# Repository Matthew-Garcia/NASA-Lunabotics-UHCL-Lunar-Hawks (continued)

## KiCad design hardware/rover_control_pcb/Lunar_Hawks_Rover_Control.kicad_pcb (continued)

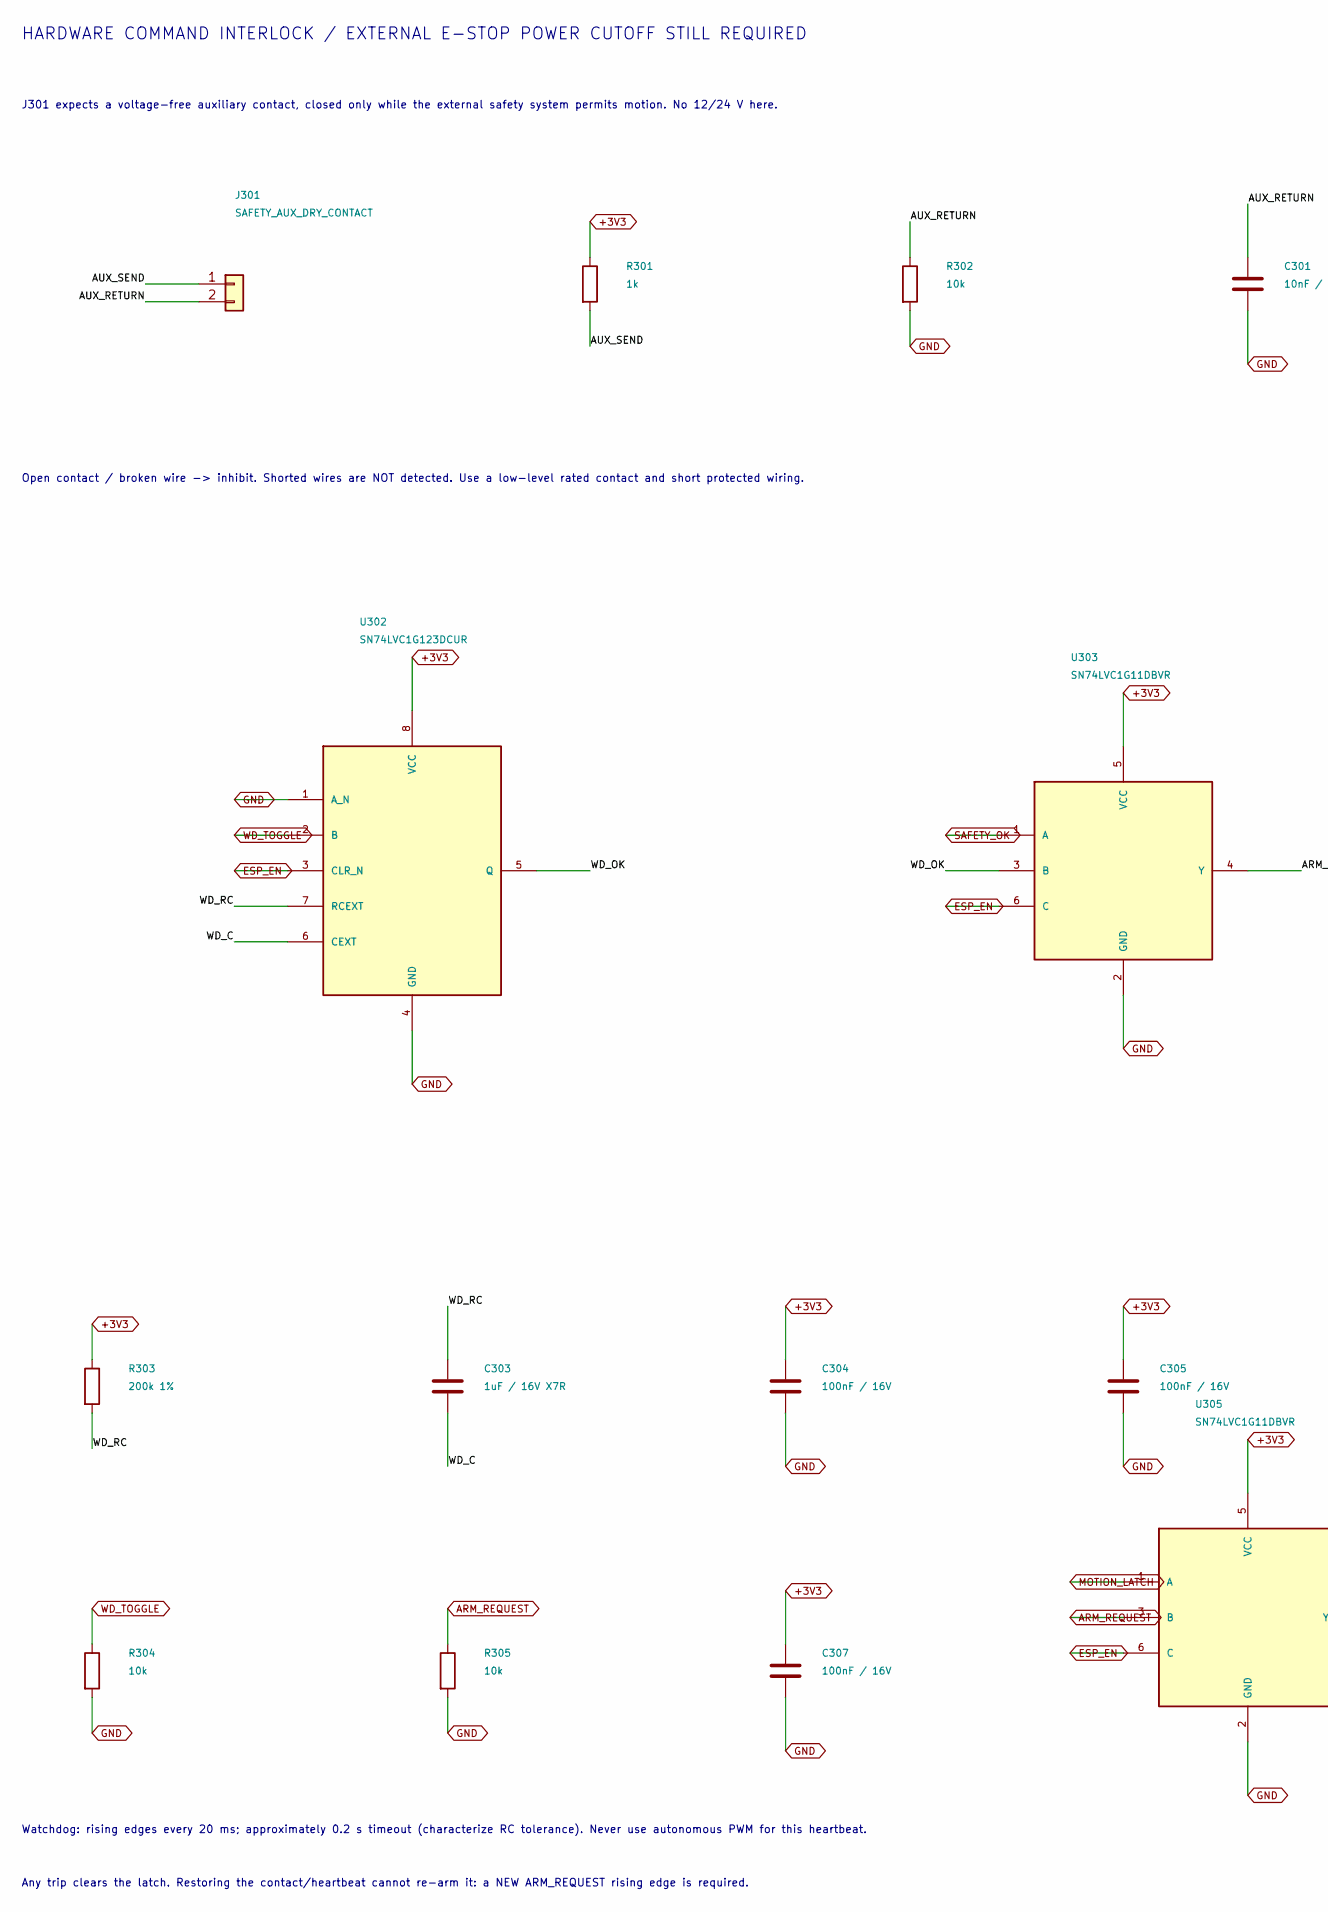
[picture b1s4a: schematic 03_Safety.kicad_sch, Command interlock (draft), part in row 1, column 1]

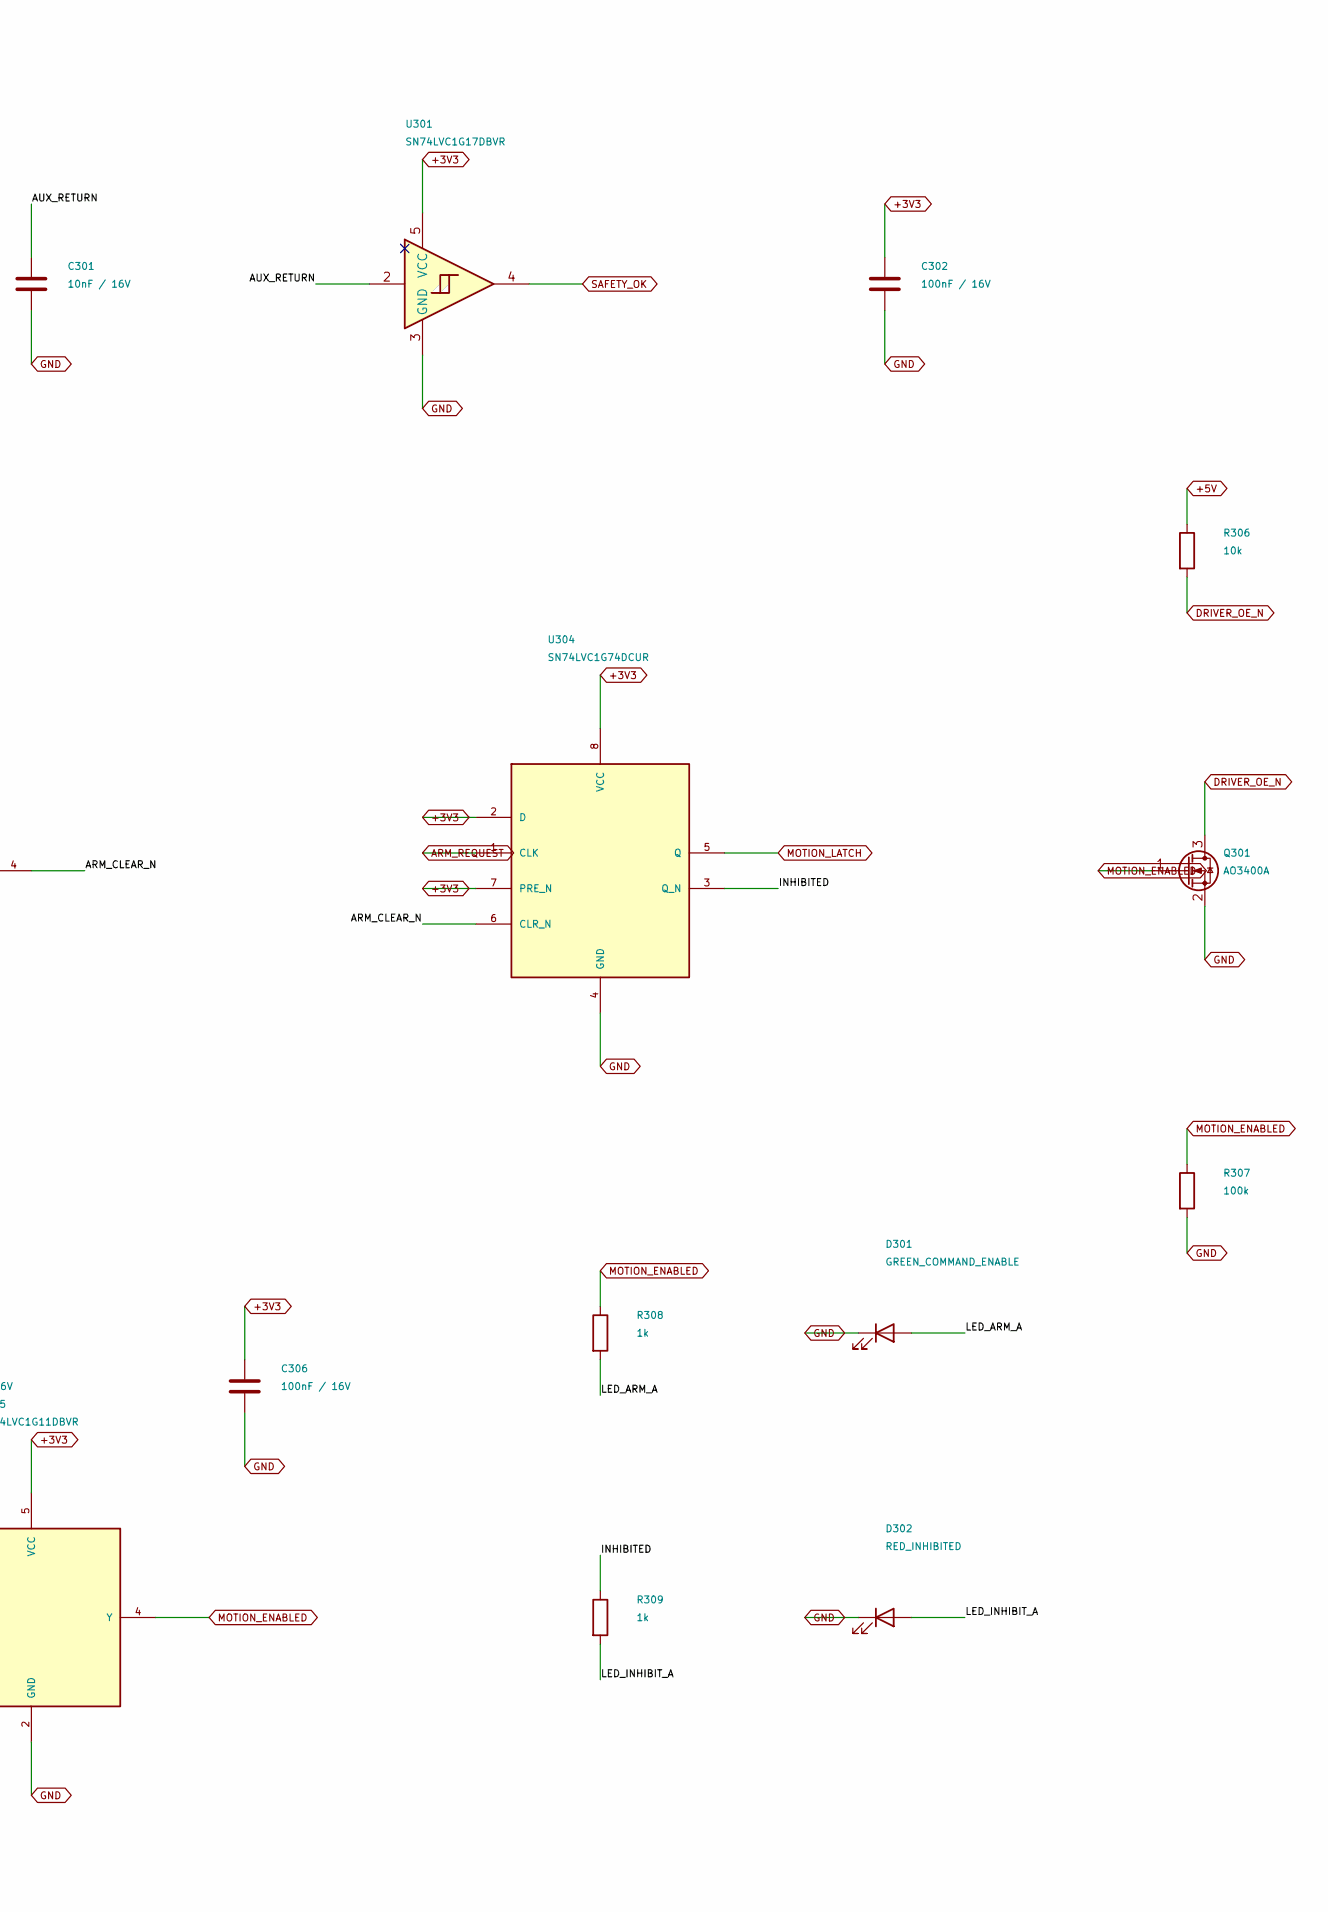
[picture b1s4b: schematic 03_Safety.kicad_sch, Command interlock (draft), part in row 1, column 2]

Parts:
C301: 10nF / 16V; C_0603_1608Metric
C302, C304, C305, C306, C307: 100nF / 16V; C_0603_1608Metric
C303: 1uF / 16V X7R; C_0603_1608Metric
D301: GREEN_COMMAND_ENABLE; LED_0603_1608Metric
D302: RED_INHIBITED; LED_0603_1608Metric
J301: SAFETY_AUX_DRY_CONTACT; TerminalBlock_Phoenix_MKDS-1,5-2_1x02_P5.00mm_Horizontal
Q301: AO3400A; SOT-23
R301, R308, R309: 1k; R_0603_1608Metric
R302, R304, R305, R306: 10k; R_0603_1608Metric
R303: 200k 1%; R_0603_1608Metric
R307: 100k; R_0603_1608Metric
U301: SN74LVC1G17DBVR; SOT-23-5
U302: SN74LVC1G123DCUR; VSSOP-8_2.3x2mm_P0.5mm
U303, U305: SN74LVC1G11DBVR; SOT-23-6
U304: SN74LVC1G74DCUR; VSSOP-8_2.3x2mm_P0.5mm

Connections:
+3V3: C302.1, C304.1, C305.1, C306.1, C307.1, R301.1, R303.1, U301.5 (VCC), U302.8 (VCC), U303.5 (VCC), U304.2 (D), U304.7 (PRE_N), U304.8 (VCC), U305.5 (VCC); also elsewhere on the board
+5V: R306.1; also elsewhere on the board
/Hardware E-stop/ARM_CLEAR_N: U303.4 (Y), U304.6 (CLR_N)
/Hardware E-stop/AUX_RETURN: C301.1, J301.2, R302.1, U301.2
/Hardware E-stop/AUX_SEND: J301.1, R301.2
/Hardware E-stop/INHIBITED: R309.1, U304.3 (Q_N)
/Hardware E-stop/LED_ARM_A: D301.2 (A), R308.2
/Hardware E-stop/LED_INHIBIT_A: D302.2 (A), R309.2
/Hardware E-stop/WD_C: C303.2, U302.6 (CEXT)
/Hardware E-stop/WD_OK: U302.5 (Q), U303.3 (B)
/Hardware E-stop/WD_RC: C303.1, R303.2, U302.7 (RCEXT)
ARM_REQUEST: R305.1, U304.1 (CLK), U305.3 (B); also elsewhere on the board
DRIVER_OE_N: Q301.3 (D), R306.2; also elsewhere on the board
ESP_EN: U302.3 (CLR_N), U303.6 (C), U305.6 (C); also elsewhere on the board
GND: C301.2, C302.2, C304.2, C305.2, C306.2, C307.2, D301.1 (K), D302.1 (K), Q301.2 (S), R302.2, R304.2, R305.2, R307.2, U301.3 (GND), U302.1 (A_N), U302.4 (GND), U303.2 (GND), U304.4 (GND), U305.2 (GND); also elsewhere on the board
MOTION_ENABLED: Q301.1 (G), R307.1, R308.1, U305.4 (Y); also elsewhere on the board
MOTION_LATCH: U304.5 (Q), U305.1 (A)
SAFETY_OK: U301.4, U303.1 (A); also elsewhere on the board
WD_TOGGLE: R304.1, U302.2 (B); also elsewhere on the board

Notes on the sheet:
HARDWARE COMMAND INTERLOCK / EXTERNAL E-STOP POWER CUTOFF STILL REQUIRED
J301 expects a voltage-free auxiliary contact, closed only while the external safety system permits motion. No 12/24 V here.
Open contact / broken wire -> inhibit. Shorted wires are NOT detected. Use a low-level rated contact and short protected wiring.
Watchdog: rising edges every 20 ms; approximately 0.2 s timeout (characterize RC tolerance). Never use autonomous PWM for this heartbeat.
Any trip clears the latch. Restoring the contact/heartbeat cannot re-arm it: a NEW ARM_REQUEST rising edge is required.

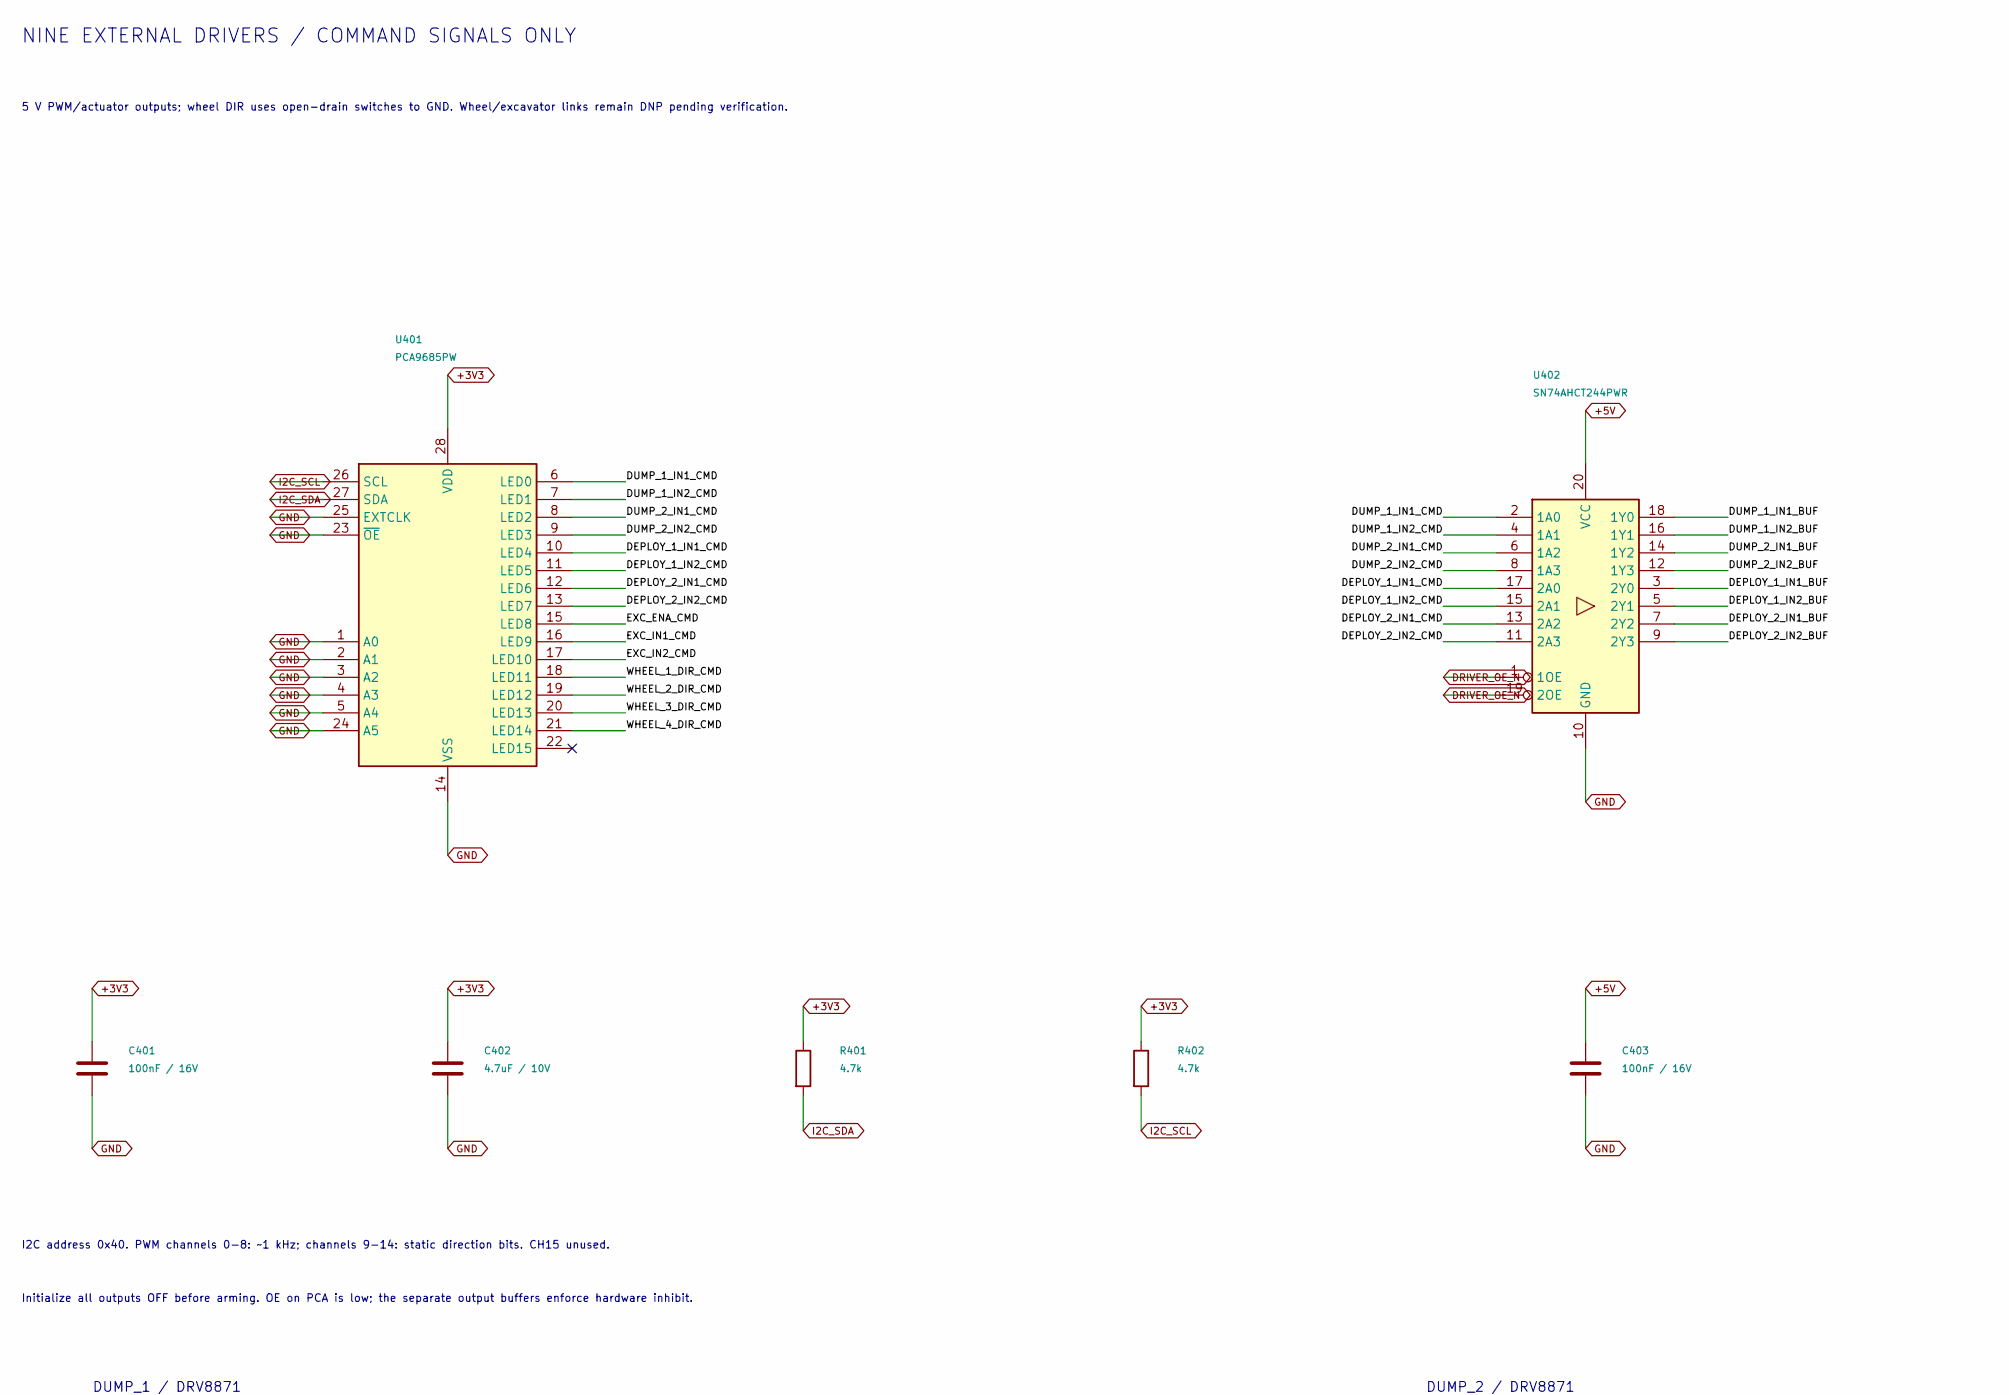
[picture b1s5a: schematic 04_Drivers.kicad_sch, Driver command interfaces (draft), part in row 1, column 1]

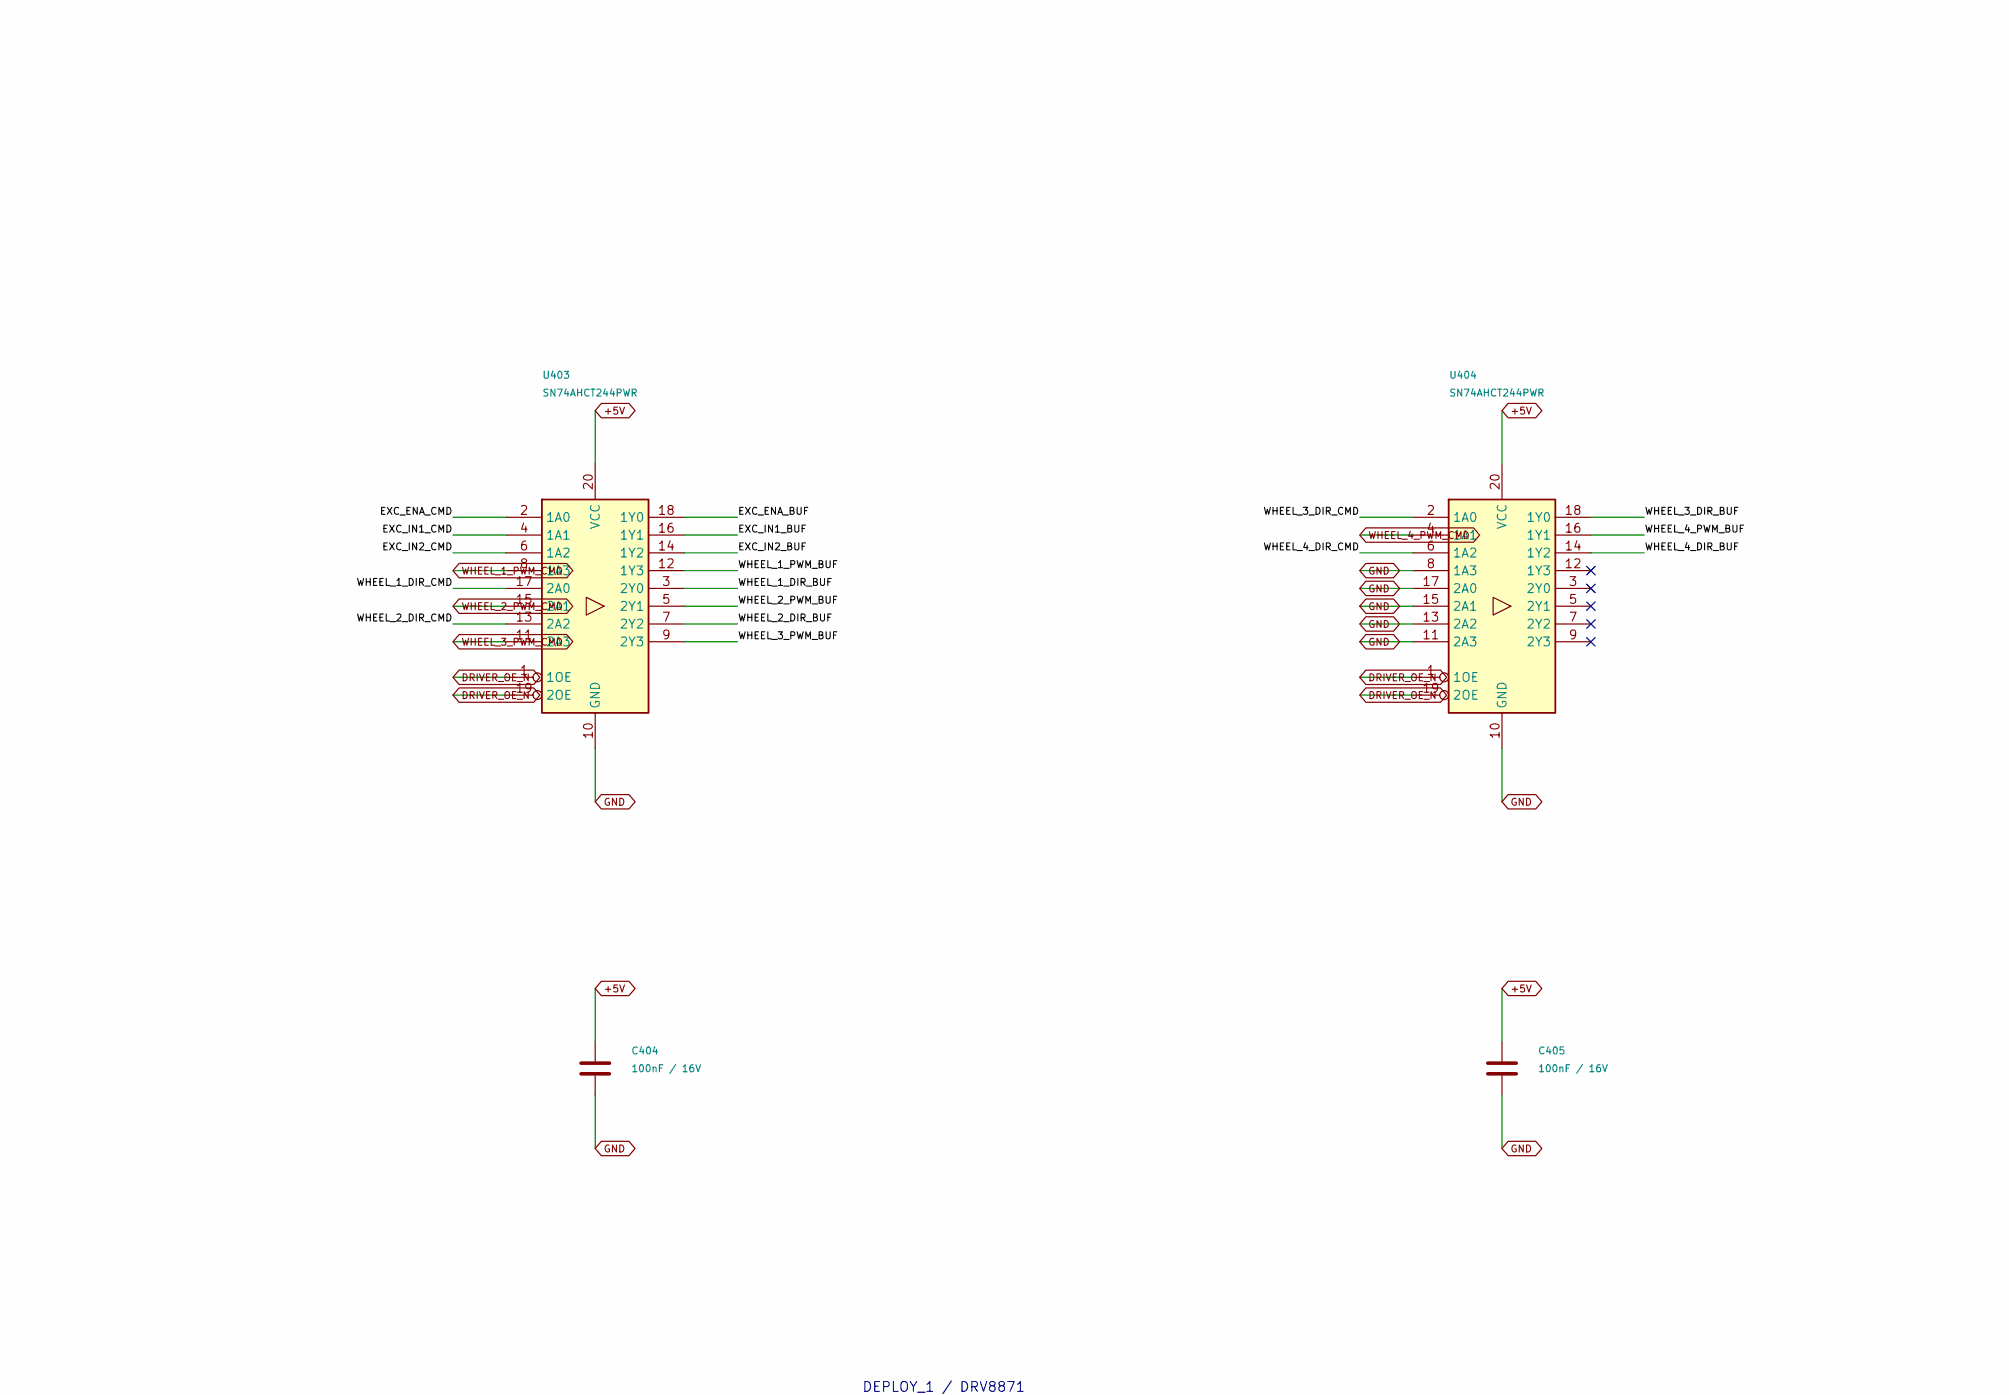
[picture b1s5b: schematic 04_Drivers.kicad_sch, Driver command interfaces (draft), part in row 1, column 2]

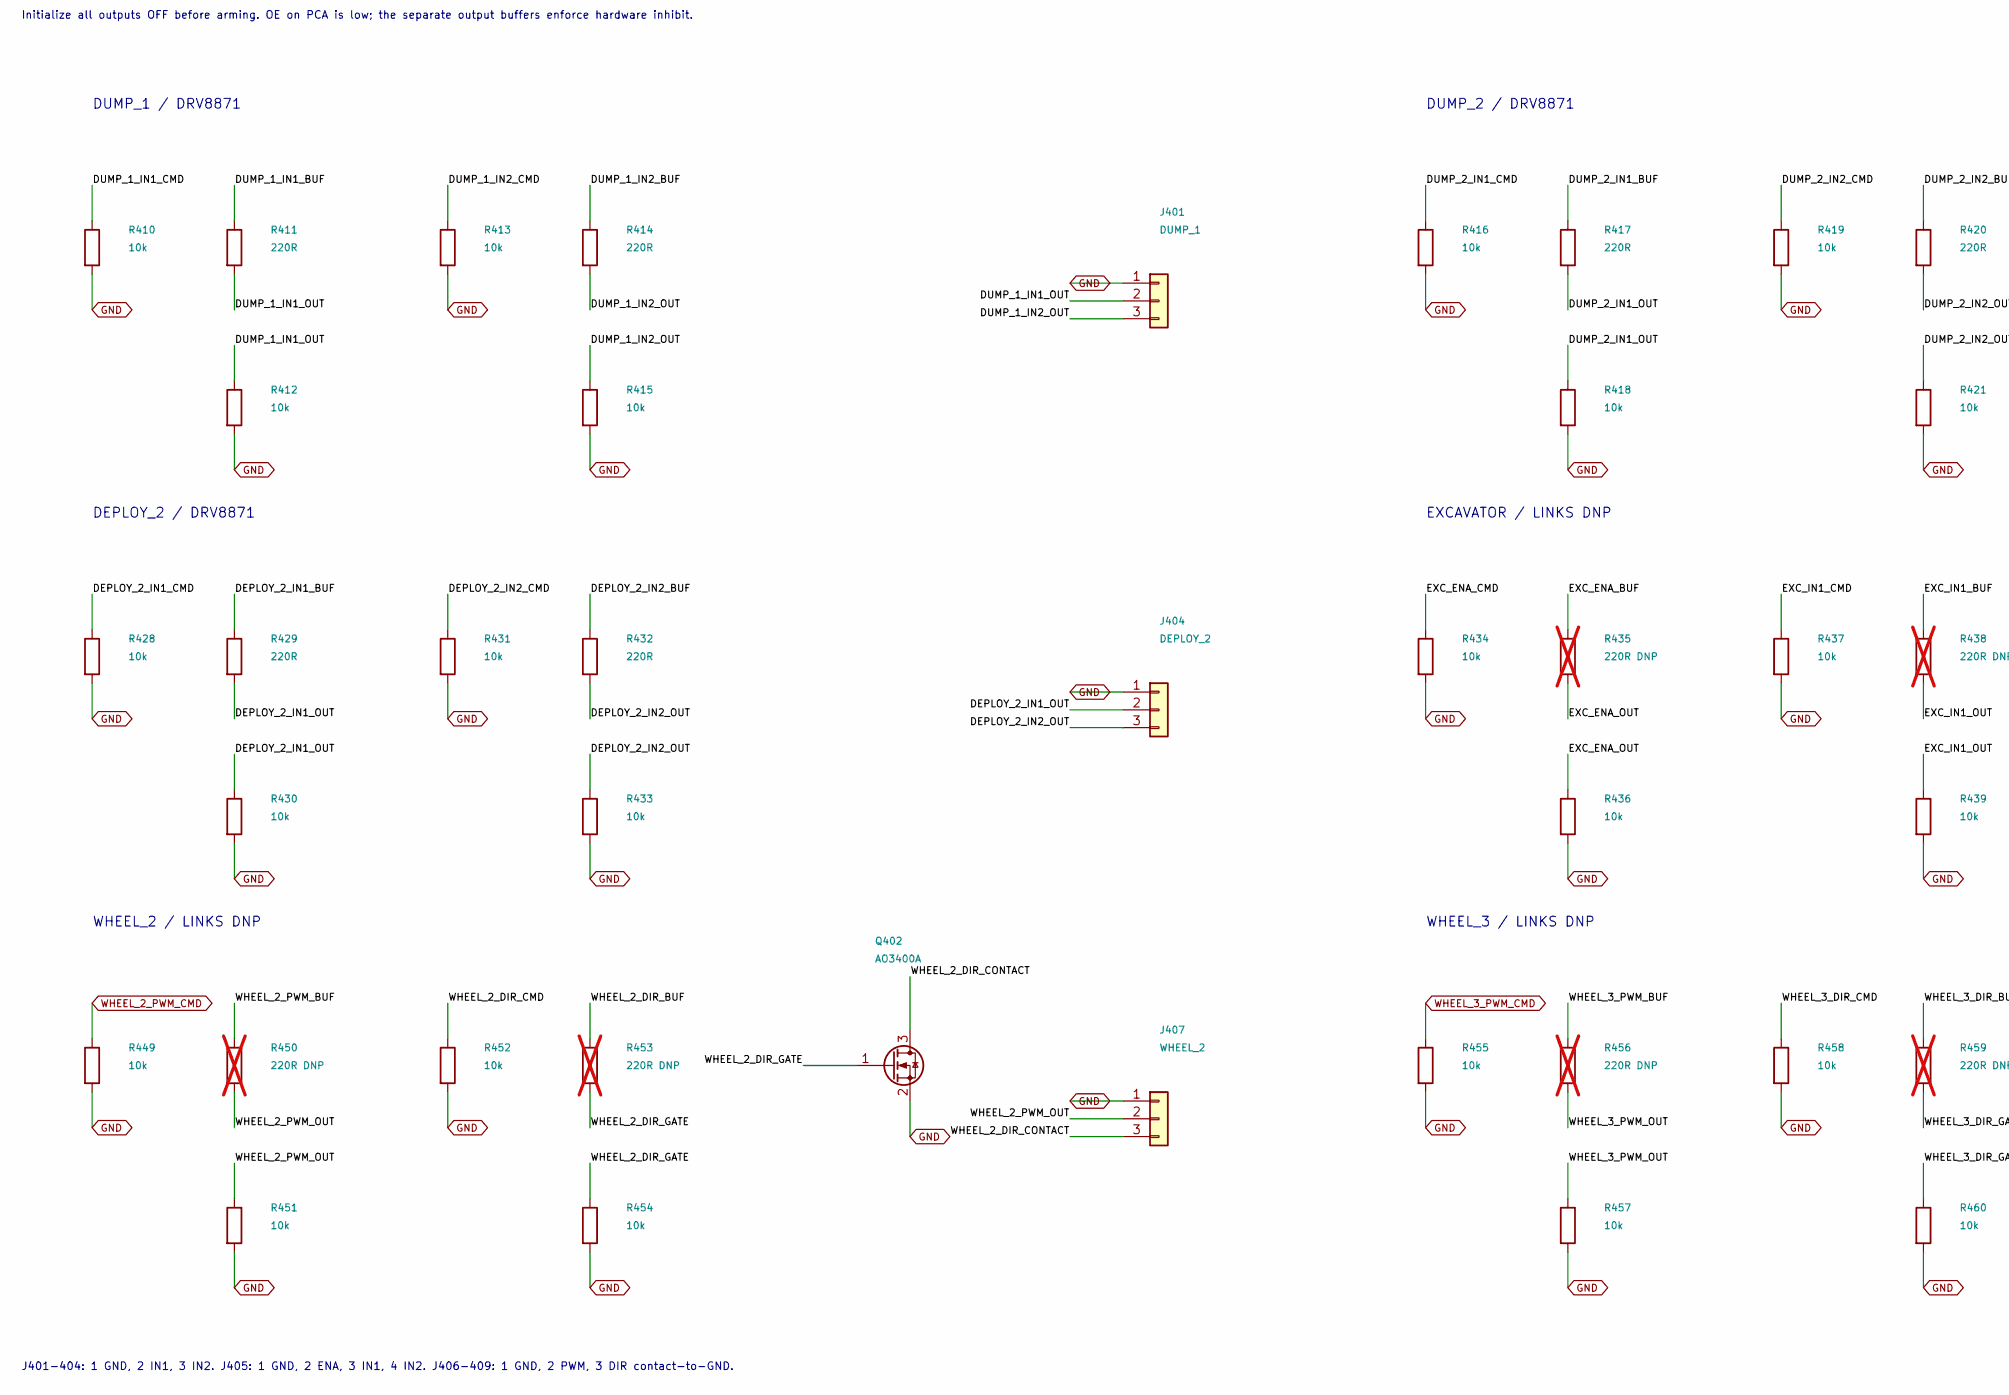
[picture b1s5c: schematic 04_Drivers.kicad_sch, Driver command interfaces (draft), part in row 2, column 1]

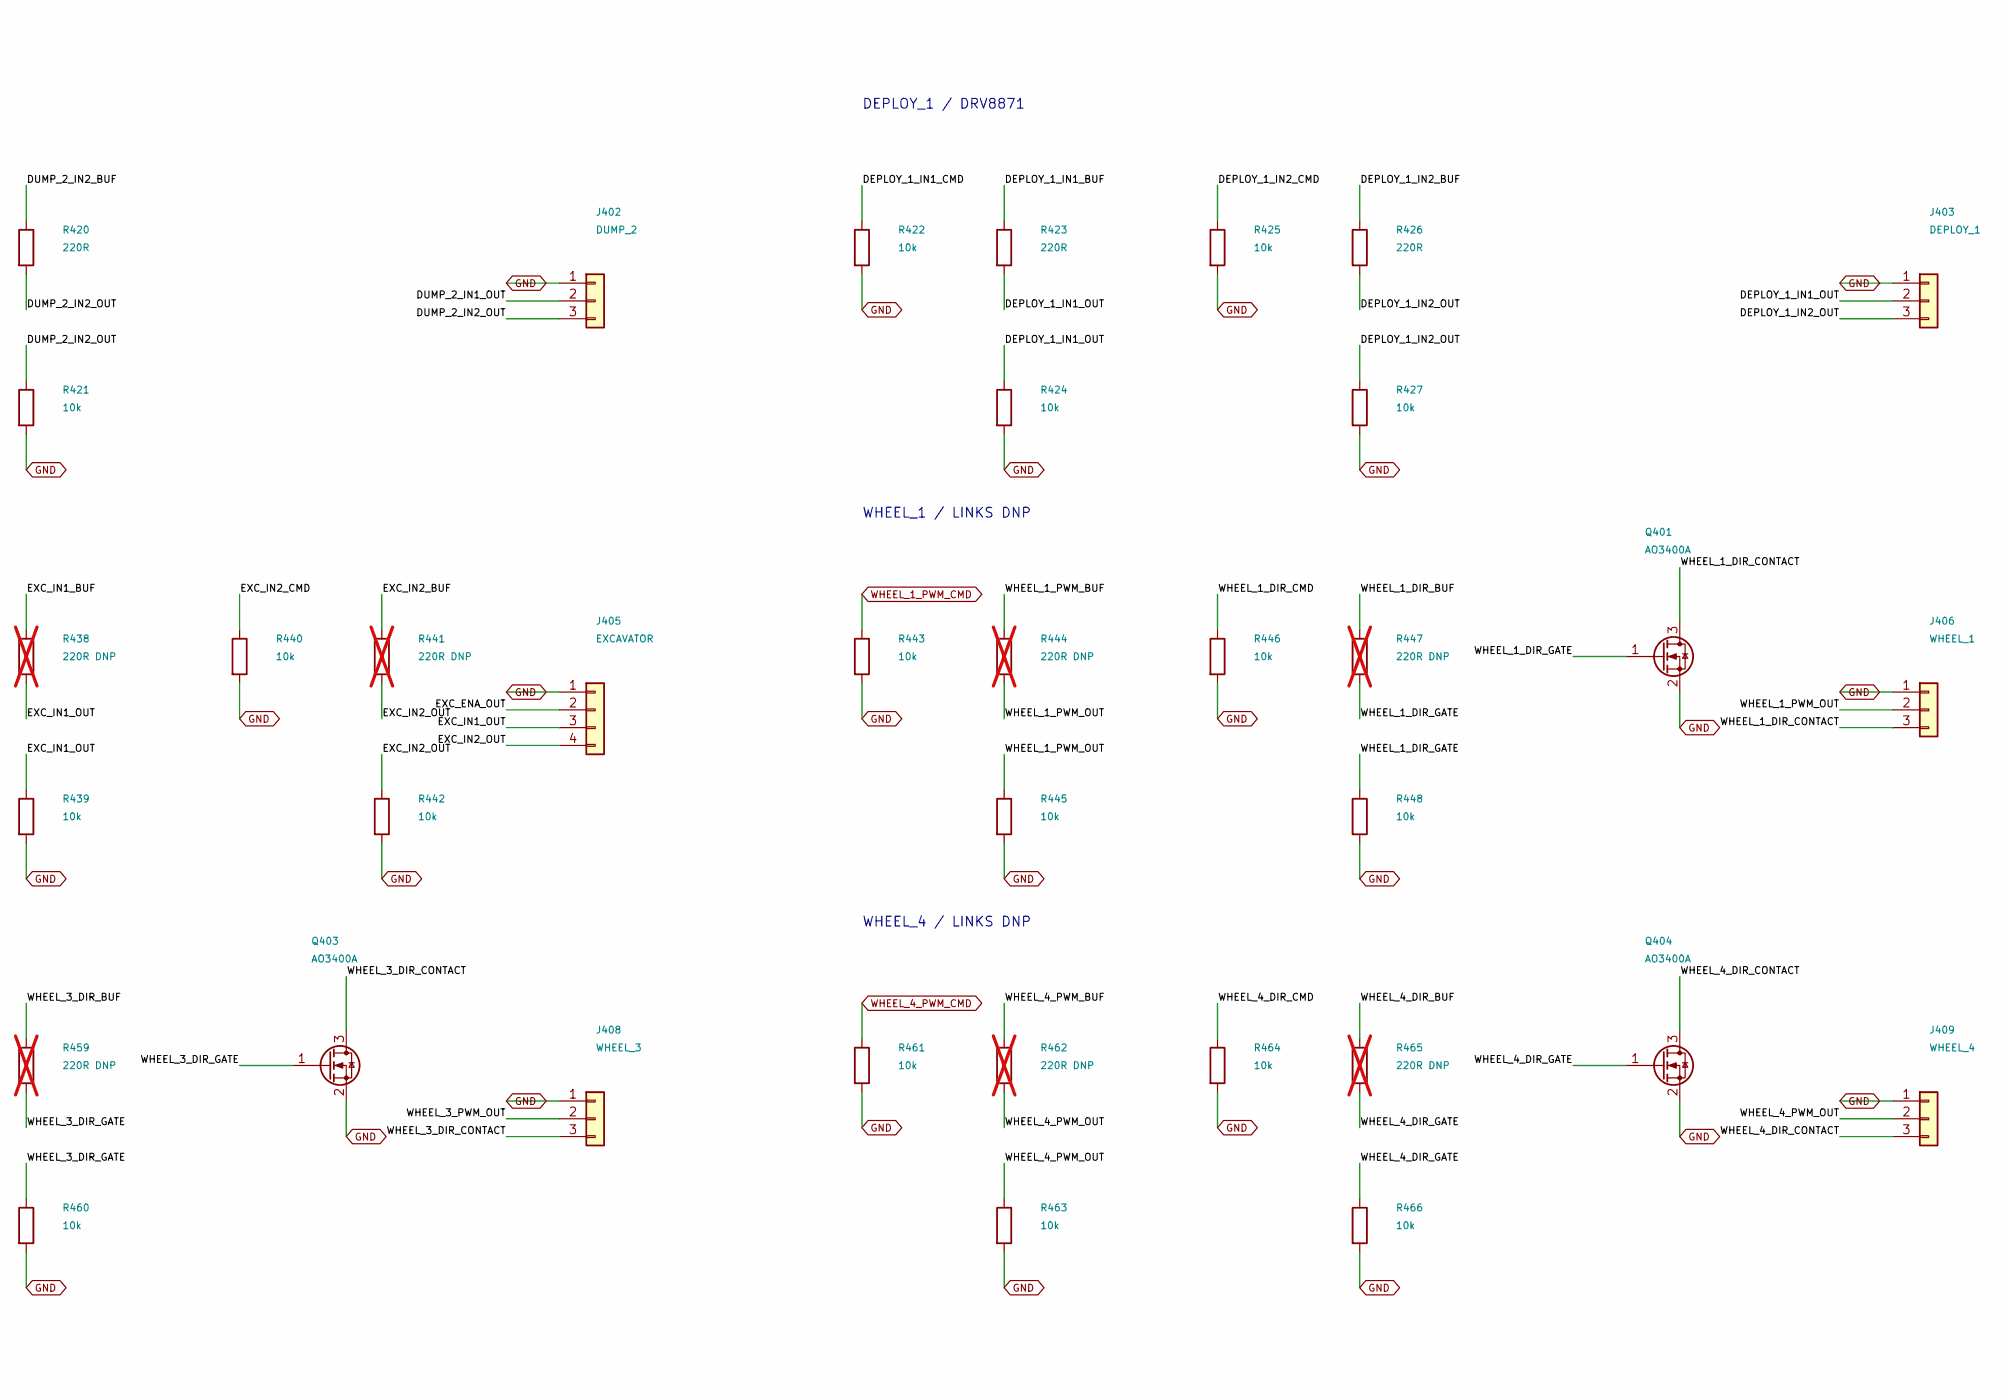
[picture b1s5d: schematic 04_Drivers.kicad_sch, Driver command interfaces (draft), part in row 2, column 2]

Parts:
C401, C403, C404, C405: 100nF / 16V; C_0603_1608Metric
C402: 4.7uF / 10V; C_0603_1608Metric
J401: DUMP_1; PinHeader_1x03_P2.54mm_Vertical
J402: DUMP_2; PinHeader_1x03_P2.54mm_Vertical
J403: DEPLOY_1; PinHeader_1x03_P2.54mm_Vertical
J404: DEPLOY_2; PinHeader_1x03_P2.54mm_Vertical
J405: EXCAVATOR; PinHeader_1x04_P2.54mm_Vertical
J406: WHEEL_1; PinHeader_1x03_P2.54mm_Vertical
J407: WHEEL_2; PinHeader_1x03_P2.54mm_Vertical
J408: WHEEL_3; PinHeader_1x03_P2.54mm_Vertical
J409: WHEEL_4; PinHeader_1x03_P2.54mm_Vertical
Q401, Q402, Q403, Q404: AO3400A; SOT-23
R401, R402: 4.7k; R_0603_1608Metric
R410, R412, R413, R415, R416, R418, R419, R421, R422, R424, R425, R427, R428, R430, R431, R433, R434, R436, R437, R439, R440, R442, R443, R445, R446, R448, R449, R451, R452, R454, R455, R457, R458, R460, R461, R463, R464, R466: 10k; R_0603_1608Metric
R411, R414, R417, R420, R423, R426, R429, R432: 220R; R_0603_1608Metric
R435, R438, R441, R444, R447, R450, R453, R456, R459, R462, R465: 220R DNP; R_0603_1608Metric; not fitted
U401: PCA9685PW; TSSOP-28_4.4x9.7mm_P0.65mm
U402, U403, U404: SN74AHCT244PWR; TSSOP-20_4.4x6.5mm_P0.65mm

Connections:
+3V3: C401.1, C402.1, R401.1, R402.1, U401.28 (VDD); also elsewhere on the board
+5V: C403.1, C404.1, C405.1, U402.20 (VCC), U403.20 (VCC), U404.20 (VCC); also elsewhere on the board
/External driver interfaces/DEPLOY_1_IN1_BUF: R423.1, U402.3 (2Y0)
/External driver interfaces/DEPLOY_1_IN1_CMD: R422.1, U401.10 (LED4), U402.17 (2A0)
/External driver interfaces/DEPLOY_1_IN1_OUT: J403.2, R423.2, R424.1
/External driver interfaces/DEPLOY_1_IN2_BUF: R426.1, U402.5 (2Y1)
/External driver interfaces/DEPLOY_1_IN2_CMD: R425.1, U401.11 (LED5), U402.15 (2A1)
/External driver interfaces/DEPLOY_1_IN2_OUT: J403.3, R426.2, R427.1
/External driver interfaces/DEPLOY_2_IN1_BUF: R429.1, U402.7 (2Y2)
/External driver interfaces/DEPLOY_2_IN1_CMD: R428.1, U401.12 (LED6), U402.13 (2A2)
/External driver interfaces/DEPLOY_2_IN1_OUT: J404.2, R429.2, R430.1
/External driver interfaces/DEPLOY_2_IN2_BUF: R432.1, U402.9 (2Y3)
/External driver interfaces/DEPLOY_2_IN2_CMD: R431.1, U401.13 (LED7), U402.11 (2A3)
/External driver interfaces/DEPLOY_2_IN2_OUT: J404.3, R432.2, R433.1
/External driver interfaces/DUMP_1_IN1_BUF: R411.1, U402.18 (1Y0)
/External driver interfaces/DUMP_1_IN1_CMD: R410.1, U401.6 (LED0), U402.2 (1A0)
/External driver interfaces/DUMP_1_IN1_OUT: J401.2, R411.2, R412.1
/External driver interfaces/DUMP_1_IN2_BUF: R414.1, U402.16 (1Y1)
/External driver interfaces/DUMP_1_IN2_CMD: R413.1, U401.7 (LED1), U402.4 (1A1)
/External driver interfaces/DUMP_1_IN2_OUT: J401.3, R414.2, R415.1
/External driver interfaces/DUMP_2_IN1_BUF: R417.1, U402.14 (1Y2)
/External driver interfaces/DUMP_2_IN1_CMD: R416.1, U401.8 (LED2), U402.6 (1A2)
/External driver interfaces/DUMP_2_IN1_OUT: J402.2, R417.2, R418.1
/External driver interfaces/DUMP_2_IN2_BUF: R420.1, U402.12 (1Y3)
/External driver interfaces/DUMP_2_IN2_CMD: R419.1, U401.9 (LED3), U402.8 (1A3)
/External driver interfaces/DUMP_2_IN2_OUT: J402.3, R420.2, R421.1
/External driver interfaces/EXC_ENA_BUF: R435.1, U403.18 (1Y0)
/External driver interfaces/EXC_ENA_CMD: R434.1, U401.15 (LED8), U403.2 (1A0)
/External driver interfaces/EXC_ENA_OUT: J405.2, R435.2, R436.1
/External driver interfaces/EXC_IN1_BUF: R438.1, U403.16 (1Y1)
/External driver interfaces/EXC_IN1_CMD: R437.1, U401.16 (LED9), U403.4 (1A1)
/External driver interfaces/EXC_IN1_OUT: J405.3, R438.2, R439.1
/External driver interfaces/EXC_IN2_BUF: R441.1, U403.14 (1Y2)
/External driver interfaces/EXC_IN2_CMD: R440.1, U401.17 (LED10), U403.6 (1A2)
/External driver interfaces/EXC_IN2_OUT: J405.4, R441.2, R442.1
/External driver interfaces/WHEEL_1_DIR_BUF: R447.1, U403.3 (2Y0)
/External driver interfaces/WHEEL_1_DIR_CMD: R446.1, U401.18 (LED11), U403.17 (2A0)
/External driver interfaces/WHEEL_1_DIR_CONTACT: J406.3, Q401.3 (D)
/External driver interfaces/WHEEL_1_DIR_GATE: Q401.1 (G), R447.2, R448.1
/External driver interfaces/WHEEL_1_PWM_BUF: R444.1, U403.12 (1Y3)
/External driver interfaces/WHEEL_1_PWM_OUT: J406.2, R444.2, R445.1
/External driver interfaces/WHEEL_2_DIR_BUF: R453.1, U403.7 (2Y2)
/External driver interfaces/WHEEL_2_DIR_CMD: R452.1, U401.19 (LED12), U403.13 (2A2)
/External driver interfaces/WHEEL_2_DIR_CONTACT: J407.3, Q402.3 (D)
/External driver interfaces/WHEEL_2_DIR_GATE: Q402.1 (G), R453.2, R454.1
/External driver interfaces/WHEEL_2_PWM_BUF: R450.1, U403.5 (2Y1)
/External driver interfaces/WHEEL_2_PWM_OUT: J407.2, R450.2, R451.1
/External driver interfaces/WHEEL_3_DIR_BUF: R459.1, U404.18 (1Y0)
/External driver interfaces/WHEEL_3_DIR_CMD: R458.1, U401.20 (LED13), U404.2 (1A0)
/External driver interfaces/WHEEL_3_DIR_CONTACT: J408.3, Q403.3 (D)
/External driver interfaces/WHEEL_3_DIR_GATE: Q403.1 (G), R459.2, R460.1
/External driver interfaces/WHEEL_3_PWM_BUF: R456.1, U403.9 (2Y3)
/External driver interfaces/WHEEL_3_PWM_OUT: J408.2, R456.2, R457.1
/External driver interfaces/WHEEL_4_DIR_BUF: R465.1, U404.14 (1Y2)
/External driver interfaces/WHEEL_4_DIR_CMD: R464.1, U401.21 (LED14), U404.6 (1A2)
/External driver interfaces/WHEEL_4_DIR_CONTACT: J409.3, Q404.3 (D)
/External driver interfaces/WHEEL_4_DIR_GATE: Q404.1 (G), R465.2, R466.1
/External driver interfaces/WHEEL_4_PWM_BUF: R462.1, U404.16 (1Y1)
/External driver interfaces/WHEEL_4_PWM_OUT: J409.2, R462.2, R463.1
DRIVER_OE_N: U402.1 (1OE), U402.19 (2OE), U403.1 (1OE), U403.19 (2OE), U404.1 (1OE), U404.19 (2OE); also elsewhere on the board
GND: C401.2, C402.2, C403.2, C404.2, C405.2, J401.1, J402.1, J403.1, J404.1, J405.1, J406.1, J407.1, J408.1, J409.1, Q401.2 (S), Q402.2 (S), Q403.2 (S), Q404.2 (S), R410.2, R412.2, R413.2, R415.2, R416.2, R418.2, R419.2, R421.2, R422.2, R424.2, R425.2, R427.2, R428.2, R430.2, R431.2, R433.2, R434.2, R436.2, R437.2, R439.2, R440.2, R442.2, R443.2, R445.2, R446.2, R448.2, R449.2, R451.2, R452.2, R454.2, R455.2, R457.2, R458.2, R460.2, R461.2, R463.2, R464.2, R466.2, U401.1 (A0), U401.2 (A1), U401.3 (A2), U401.4 (A3), U401.5 (A4), U401.14 (VSS), U401.23 (~OE), U401.24 (A5), U401.25 (EXTCLK), U402.10 (GND), U403.10 (GND), U404.8 (1A3), U404.10 (GND), U404.11 (2A3), U404.13 (2A2), U404.15 (2A1), U404.17 (2A0); also elsewhere on the board
I2C_SCL: R402.2, U401.26 (SCL); also elsewhere on the board
I2C_SDA: R401.2, U401.27 (SDA); also elsewhere on the board
WHEEL_1_PWM_CMD: R443.1, U403.8 (1A3); also elsewhere on the board
WHEEL_2_PWM_CMD: R449.1, U403.15 (2A1); also elsewhere on the board
WHEEL_3_PWM_CMD: R455.1, U403.11 (2A3); also elsewhere on the board
WHEEL_4_PWM_CMD: R461.1, U404.4 (1A1); also elsewhere on the board

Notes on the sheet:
NINE EXTERNAL DRIVERS / COMMAND SIGNALS ONLY
5 V PWM/actuator outputs; wheel DIR uses open-drain switches to GND. Wheel/excavator links remain DNP pending verification.
I2C address 0x40. PWM channels 0-8: ~1 kHz; channels 9-14: static direction bits. CH15 unused.
Initialize all outputs OFF before arming. OE on PCA is low; the separate output buffers enforce hardware inhibit.
DUMP_1 / DRV8871
DUMP_2 / DRV8871
DEPLOY_1 / DRV8871
DEPLOY_2 / DRV8871
EXCAVATOR / LINKS DNP
WHEEL_1 / LINKS DNP
WHEEL_2 / LINKS DNP
WHEEL_3 / LINKS DNP
WHEEL_4 / LINKS DNP
J401-404: 1 GND, 2 IN1, 3 IN2. J405: 1 GND, 2 ENA, 3 IN1, 4 IN2. J406-409: 1 GND, 2 PWM, 3 DIR contact-to-GND.

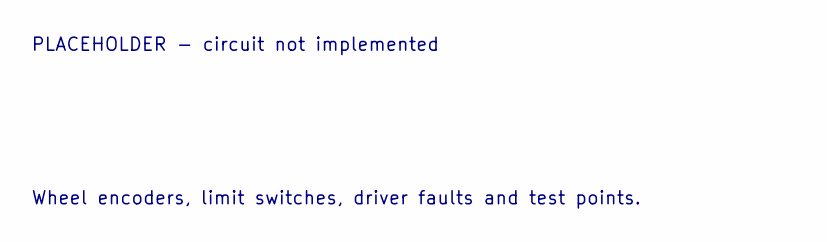
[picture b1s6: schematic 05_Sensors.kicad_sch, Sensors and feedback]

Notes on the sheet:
PLACEHOLDER - circuit not implemented
Wheel encoders, limit switches, driver faults and test points.
